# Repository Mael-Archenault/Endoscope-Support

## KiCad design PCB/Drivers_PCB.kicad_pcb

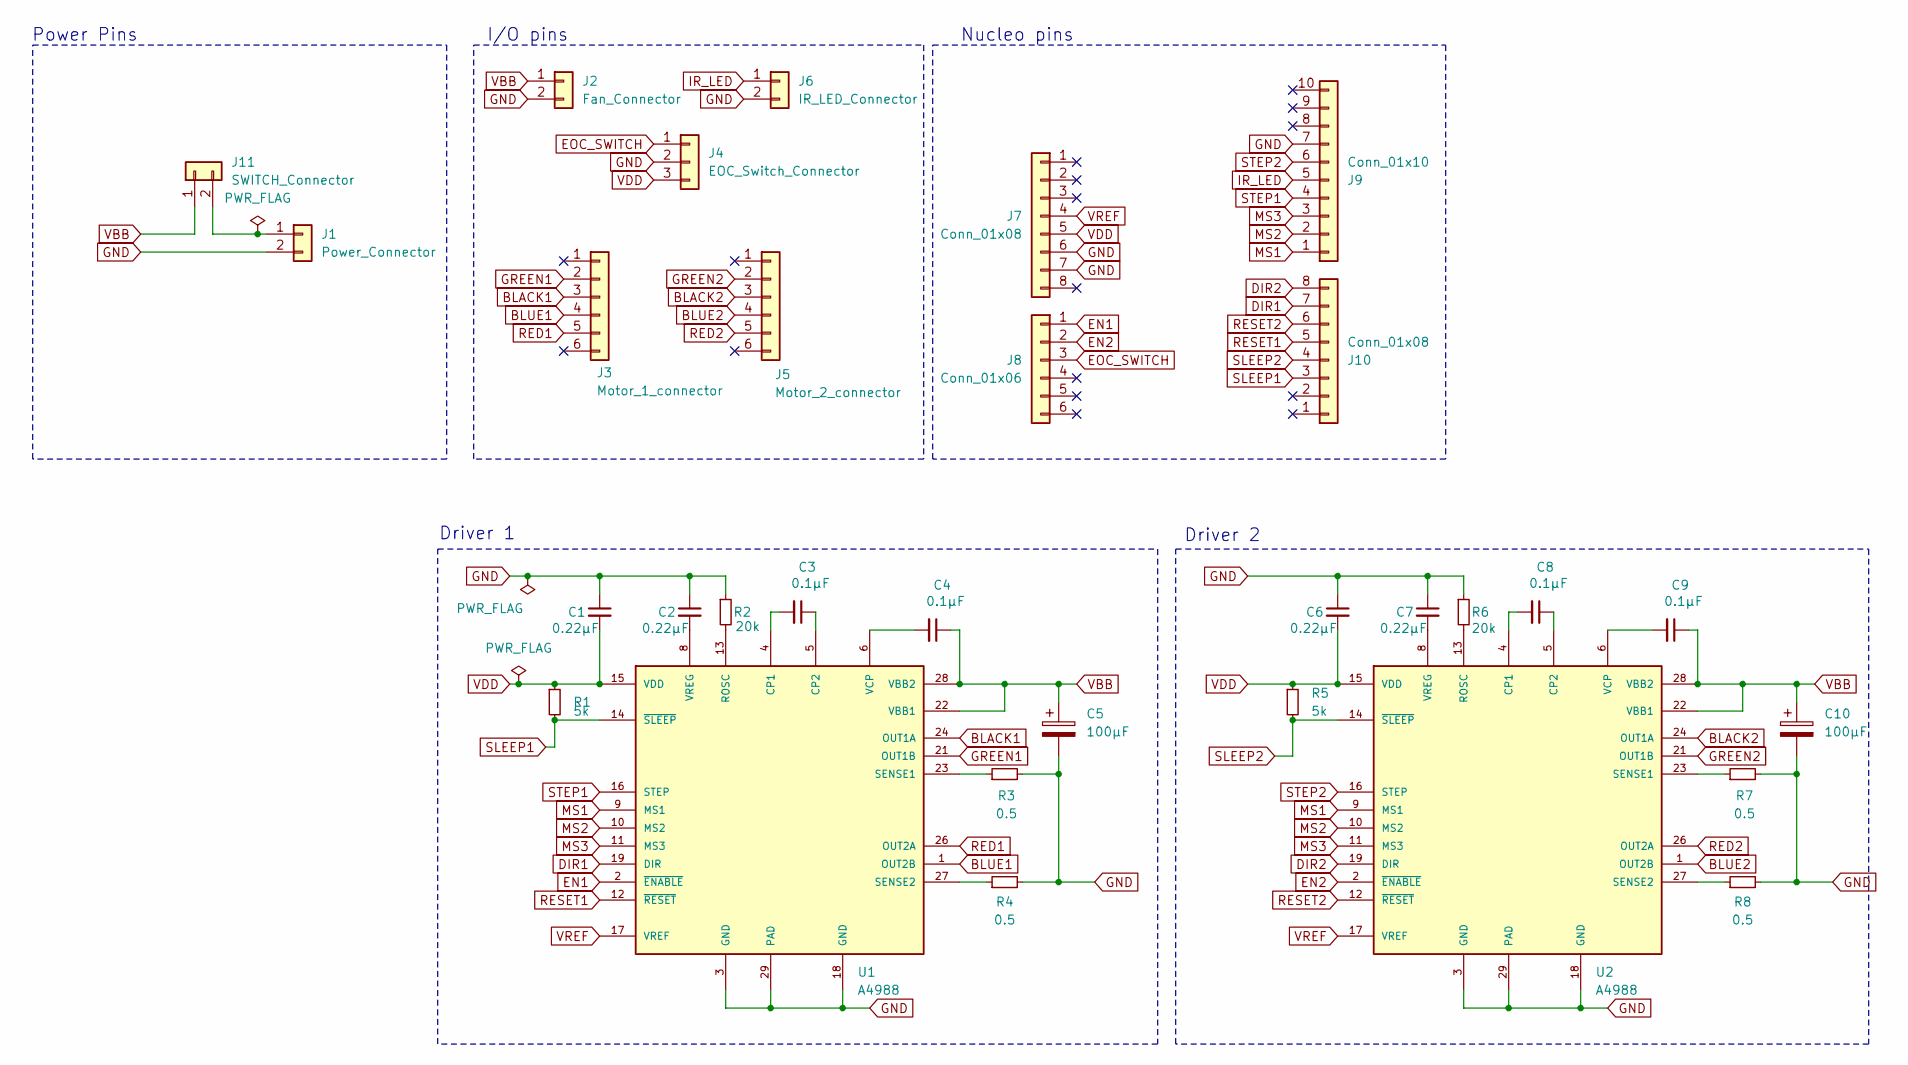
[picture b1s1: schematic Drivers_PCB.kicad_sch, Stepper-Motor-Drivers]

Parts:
C1, C2, C6, C7: 0.22µF; C_0805_2012Metric_Pad1.18x1.45mm_HandSolder
C3, C4, C8, C9: 0.1µF; C_0805_2012Metric_Pad1.18x1.45mm_HandSolder
C5, C10: 100µF; Alimentation_Capacitor
J1: Power_Connector; TerminalBlock_bornier-2_P5.08mm
J2: Fan_Connector; JST_XH_B2B-XH-A_1x02_P2.50mm_Vertical
J3: Motor_1_connector; JST_XH_B6B-XH-A_1x06_P2.50mm_Vertical
J4: EOC_Switch_Connector; JST_XH_B3B-XH-A_1x03_P2.50mm_Vertical
J5: Motor_2_connector; JST_XH_B6B-XH-A_1x06_P2.50mm_Vertical
J6: IR_LED_Connector; JST_XH_B2B-XH-A_1x02_P2.50mm_Vertical
J7, J10: Conn_01x08; PinHeader_1x08_P2.54mm_Vertical
J8: Conn_01x06; PinHeader_1x06_P2.54mm_Vertical
J9: Conn_01x10; PinHeader_1x10_P2.54mm_Vertical
J11: SWITCH_Connector; JST_XH_B2B-XH-A_1x02_P2.50mm_Vertical
R1, R5: 5k; R_0805_2012Metric_Pad1.20x1.40mm_HandSolder
R2, R6: 20k; R_0805_2012Metric_Pad1.20x1.40mm_HandSolder
R3, R4, R7, R8: 0.5; R_0805_2012Metric_Pad1.20x1.40mm_HandSolder
U1, U2: A4988

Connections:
BLACK1: J3.3, U1.24 (OUT1A)
BLACK2: J5.3, U2.24 (OUT1A)
BLUE1: J3.4, U1.1 (OUT2B)
BLUE2: J5.4, U2.1 (OUT2B)
DIR1: J10.7, U1.19 (DIR)
DIR2: J10.8, U2.19 (DIR)
EN1: J8.1, U1.2 (~ENABLE)
EN2: J8.2, U2.2 (~ENABLE)
EOC_SWITCH: J4.1, J8.3
GND: C1.1, C2.1, C5.2, C6.1, C7.1, C10.2, J1.2, J2.2, J4.2, J6.2, J7.6, J7.7, J9.7, R2.1, R3.2, R4.2, R6.1, R7.2, R8.2, U1.3 (GND), U1.18 (GND), U1.29 (PAD), U2.3 (GND), U2.18 (GND), U2.29 (PAD)
GREEN1: J3.2, U1.21 (OUT1B)
GREEN2: J5.2, U2.21 (OUT1B)
IR_LED: J6.1, J9.5
MS1: J9.1, U1.9 (MS1), U2.9 (MS1)
MS2: J9.2, U1.10 (MS2), U2.10 (MS2)
MS3: J9.3, U1.11 (MS3), U2.11 (MS3)
unnamed: J1.1, J11.2
unnamed: C3.2, U1.4 (CP1)
unnamed: C3.1, U1.5 (CP2)
unnamed: R2.2, U1.13 (ROSC)
unnamed: R3.1, U1.23 (SENSE1)
unnamed: R4.1, U1.27 (SENSE2)
unnamed: C4.2, U1.6 (VCP)
unnamed: C2.2, U1.8 (VREG)
unnamed: C8.2, U2.4 (CP1)
unnamed: C8.1, U2.5 (CP2)
unnamed: R6.2, U2.13 (ROSC)
unnamed: R7.1, U2.23 (SENSE1)
unnamed: R8.1, U2.27 (SENSE2)
unnamed: C9.2, U2.6 (VCP)
unnamed: C7.2, U2.8 (VREG)
RED1: J3.5, U1.26 (OUT2A)
RED2: J5.5, U2.26 (OUT2A)
RESET1: J10.5, U1.12 (~RESET)
RESET2: J10.6, U2.12 (~RESET)
SLEEP1: J10.3, R1.2, U1.14 (~SLEEP)
SLEEP2: J10.4, R5.2, U2.14 (~SLEEP)
STEP1: J9.4, U1.16 (STEP)
STEP2: J9.6, U2.16 (STEP)
VBB: C4.1, C5.1, C9.1, C10.1, J2.1, J11.1, U1.22 (VBB1), U1.28 (VBB2), U2.22 (VBB1), U2.28 (VBB2)
VDD: C1.2, C6.2, J4.3, J7.5, R1.1, R5.1, U1.15 (VDD), U2.15 (VDD)
VREF: J7.4, U1.17 (VREF), U2.17 (VREF)

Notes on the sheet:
Nucleo pins
Power Pins
I/O pins
Driver 1
Driver 2

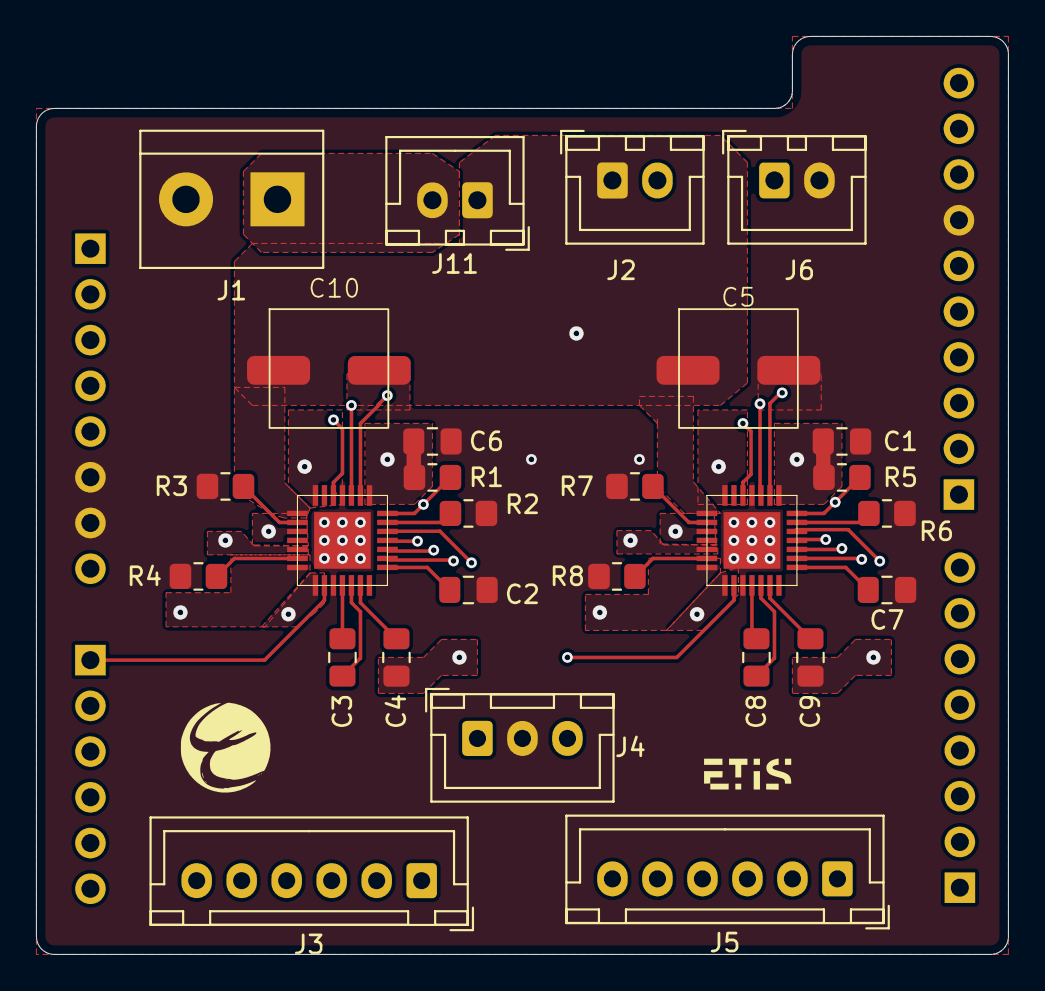
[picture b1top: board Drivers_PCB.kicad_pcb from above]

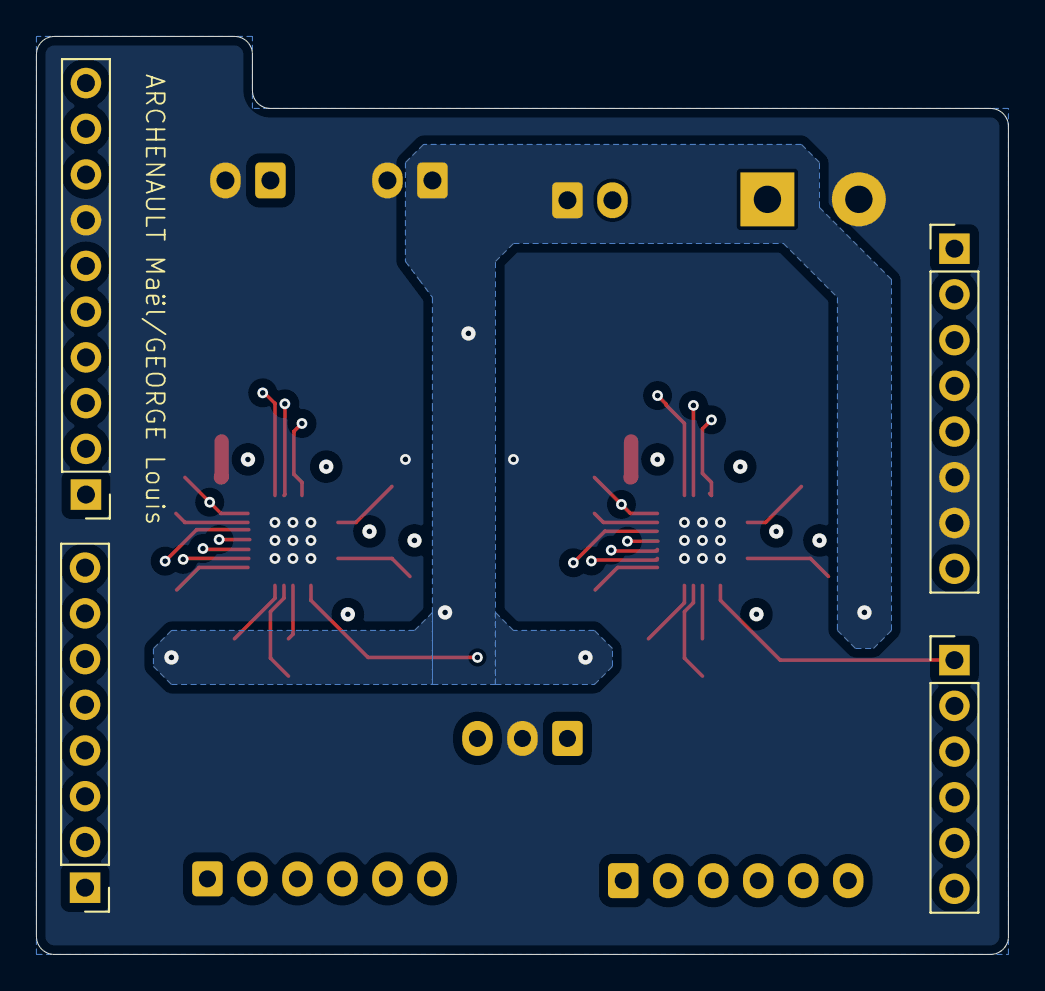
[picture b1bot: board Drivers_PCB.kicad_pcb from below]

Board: 4 copper layers, 54.0 x 51.0 mm, 31 parts (4 on the bottom side), 42 nets.

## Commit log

2024-12-21 Fixing the shield pins matching
2024-12-29 PCB update, Main STM code creation, UI creation
2025-01-05 Upgrading UI
2025-01-14 Cleaning the git
2025-01-14 Fine tuning some pieces
2025-01-20 serial communication with UI
2025-01-20 finishing PCB
2025-01-27 Assembling all rotation system
2025-01-28 Cleaning Rotation System
2025-01-28 Generating Gerber files
2025-01-28 Starting sliders
2025-02-03 Upgrading the rotation system
2025-02-04 added capture settings parameters
2025-02-04 added test parameters
2025-02-10 Finishin the Rotation System
2025-02-10 Creating Driver functions
2025-02-11 Added command to test buttons
2025-02-12 Working usart communication
2025-02-12 filling in all components values
2025-02-12 changing some buttons
2025-02-25 Cleaning the 'Capture Settings' Panel
2025-02-25 Building the global structure of the code
2025-02-25 updating useless files
2025-02-26 Deleting useless build files
2025-02-26 Cleaning the section 'Test' and fixing the sidebar
2025-02-26 Cleaning the 'Capture' Section
2025-02-26 Creating the 'Connection' Section
2025-02-27 Creating interaction between PC and STM
2025-02-28 Completing UI and Hardware code
2025-03-01 Adding color themes
2025-03-02 Added language selection
2025-03-02 Fixing problems with driver configuration pins output
2025-03-06 Adding the mode selection in Capture Settings Panel
2025-03-07 changing the words 'angles' to 'packets'
2025-03-12 Fixing the problem with the optic fiber attach
2025-03-18 Calibrating the steps + adding external 3d models (ir holder, optic fiber attach)
